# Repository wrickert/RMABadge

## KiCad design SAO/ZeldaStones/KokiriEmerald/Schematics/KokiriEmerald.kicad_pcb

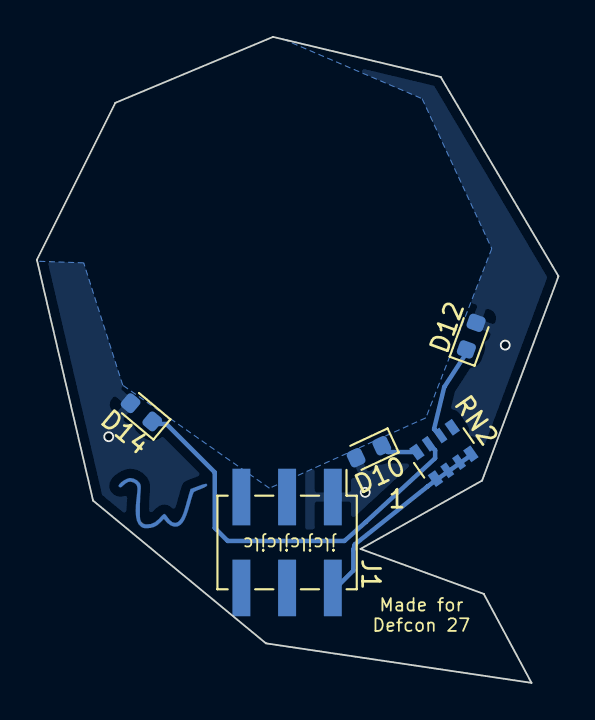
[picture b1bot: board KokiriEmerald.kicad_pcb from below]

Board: 2 copper layers, 29.0 x 35.9 mm, 6 parts (6 on the bottom side), 5 nets.

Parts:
D10, D12, D14: LED_Small; LED_0603_1608Metric
J1: Conn_02x03_Odd_Even; PinHeader_2x03_P2.54mm_Vertical_SMD
RN2: 330; R_Array_Convex_4x0603
Ref**: Val**; W

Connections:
unnamed: D12.1, RN2.2
unnamed: D14.1, RN2.3
unnamed: D10.1, RN2.4
VCC: D10.2, D12.2, D14.2, J1.1
VSS: J1.2, RN2.5, RN2.6, RN2.7, RN2.8

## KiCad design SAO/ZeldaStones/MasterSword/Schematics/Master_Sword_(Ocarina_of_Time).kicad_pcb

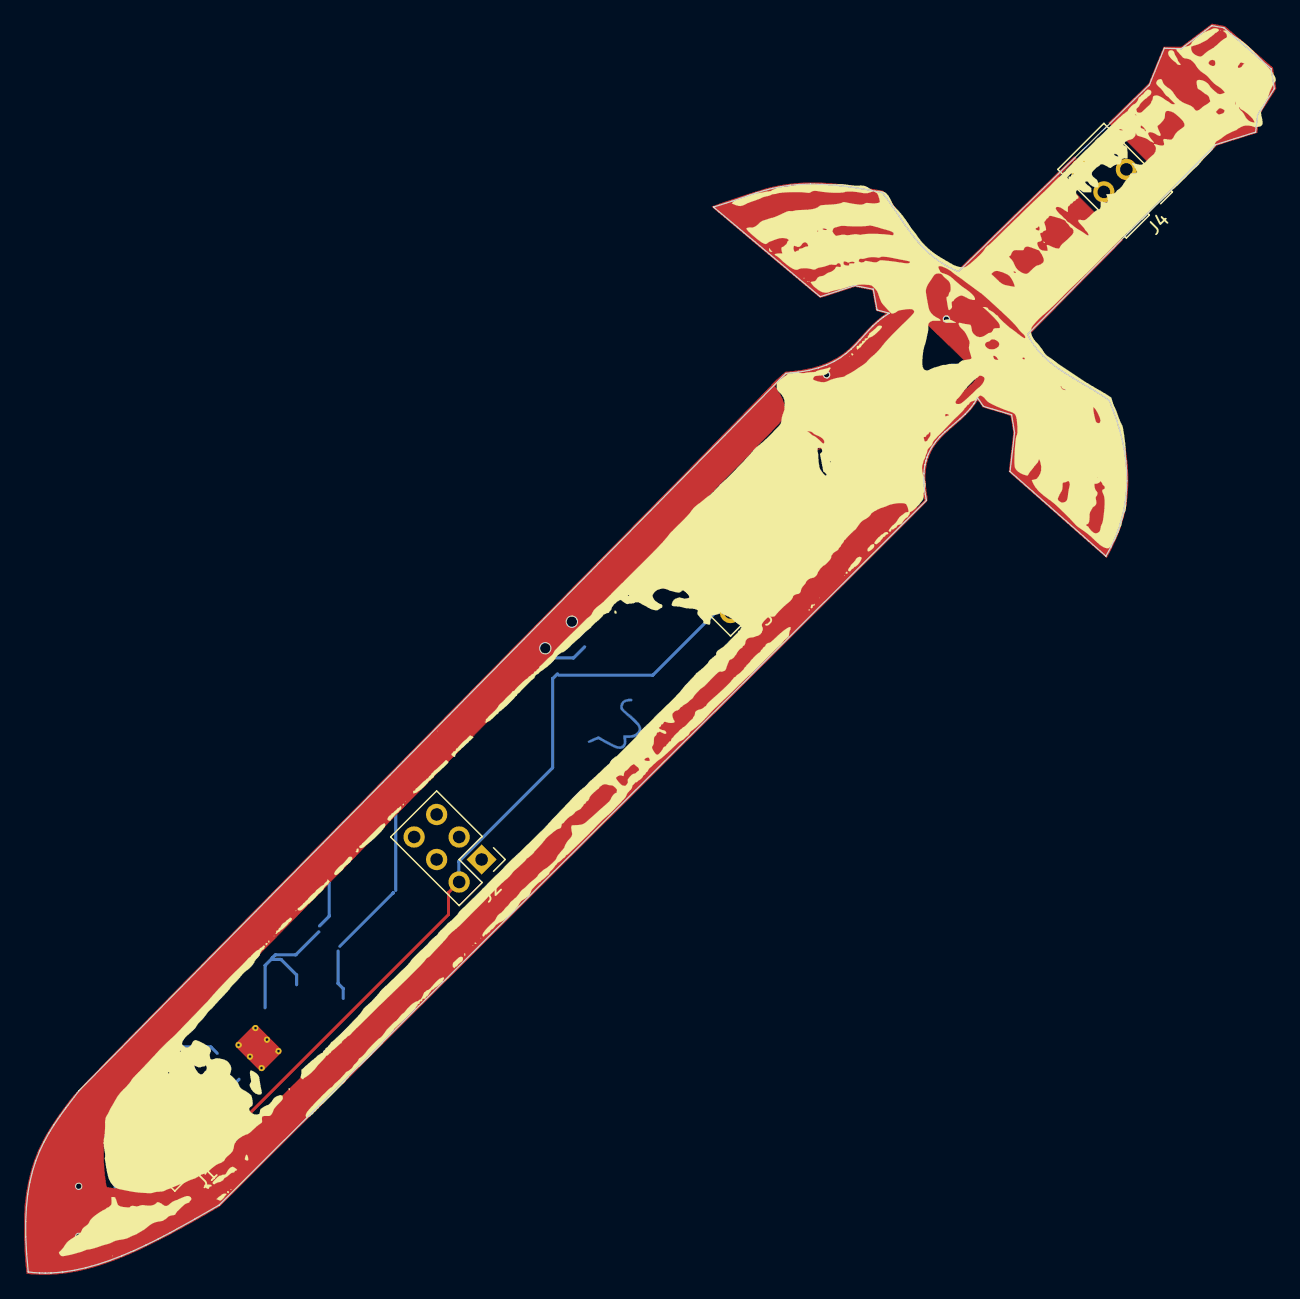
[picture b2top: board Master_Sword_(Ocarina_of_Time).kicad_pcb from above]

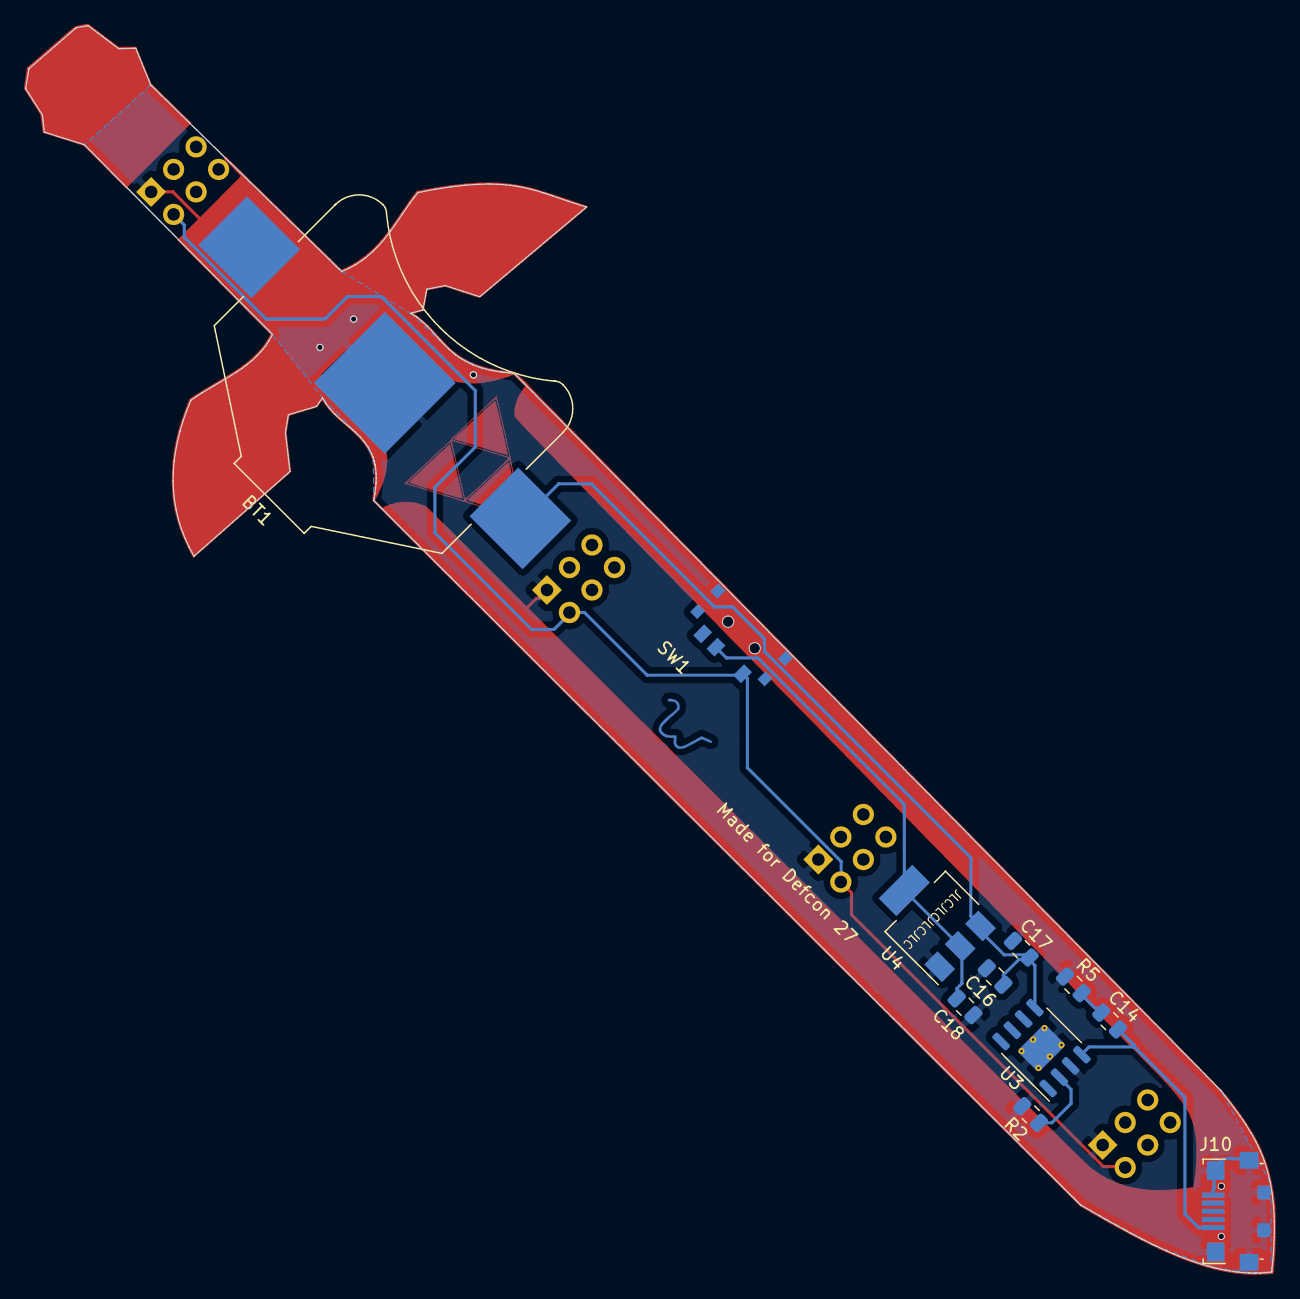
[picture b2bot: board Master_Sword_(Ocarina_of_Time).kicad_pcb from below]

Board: 2 copper layers, 99.7 x 99.6 mm, 16 parts (12 on the bottom side), 7 nets.

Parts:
BT1: Battery_Cell; BatteryHolder_Keystone_3008_1x2450
C14, C17: 10uF; C_0805_2012Metric
C16, C18: 1uF; C_0805_2012Metric
J1, J2, J3, J4: Conn_02x03_Odd_Even; PinHeader_2x03_P2.54mm_Vertical
J10: USB_B_Micro; USB_Micro-B_Jing
R2: 1k; R_0805_2012Metric
R5: 1.5; R_0805_2012Metric
Ref**: Val**; W
SW1: SW_SPDT; SK-3296S_switch
U3: HX4056; HSOP-8-1EP_3.9x4.9mm_P1.27mm_EP2.41x3.1mm_ThermalVias
U4: TLV1117-33; SOT-223-3_TabPin2

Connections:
+3V3: C18.1, SW1.2, U4.2
unnamed: C14.1, R5.2
unnamed: C14.2, J10.1, U3.4
unnamed: R2.1, U3.2
VDD: J1.2, J2.2, J3.2, J4.2, SW1.3
VDDA: BT1.1, C16.1, C17.2, U3.5, U4.3
VSS: BT1.2, C16.2, C17.1, C18.2, J1.1, J2.1, J3.1, J4.1, J10.5, J10.6, R2.2, R5.1, U3.3, U3.9, U4.1

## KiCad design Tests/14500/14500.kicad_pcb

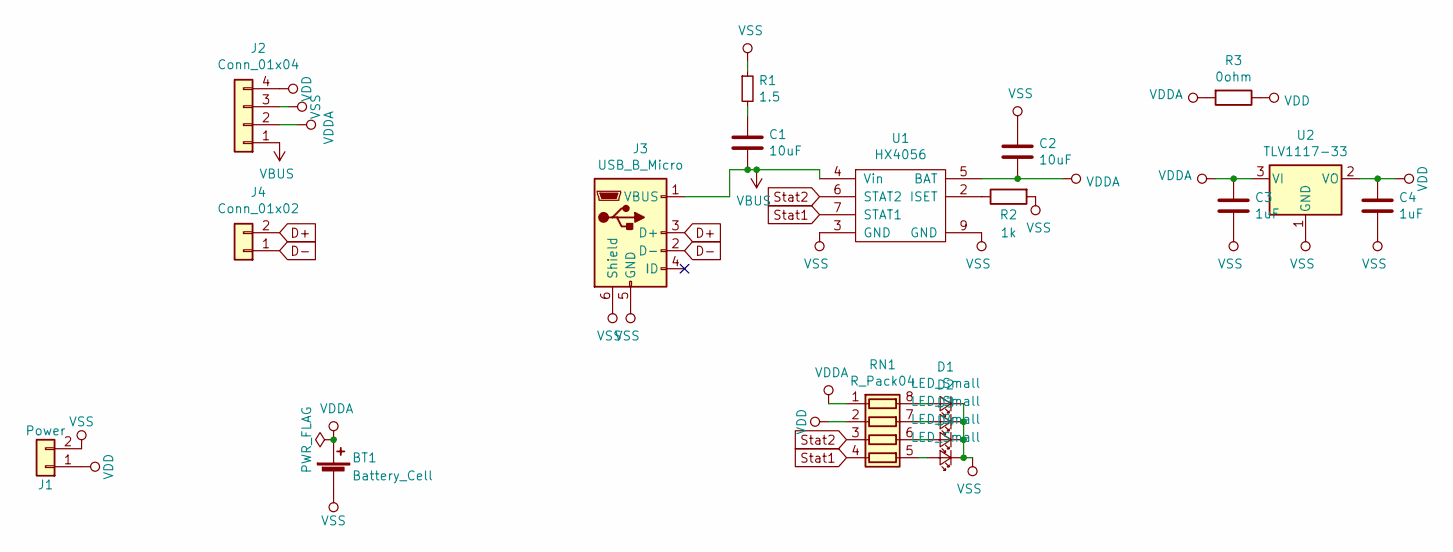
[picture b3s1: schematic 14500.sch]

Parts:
BT1: Battery_Cell; Dongguan14500
C1, C2: 10uF; C_0805_2012Metric
C3, C4: 1uF; C_0805_2012Metric
D1, D2, D3, D4: LED_Small; LED_0603_1608Metric
J1: Power; PinHeader_1x02_P2.54mm_Vertical
J2: Conn_01x04; PinHeader_1x04_P2.54mm_Vertical
J3: USB_B_Micro; USB_Micro-B_Jing
J4: Conn_01x02; PinHeader_1x02_P2.54mm_Vertical
R1: 1.5; R_0805_2012Metric
R2: 1k; R_0805_2012Metric
R3: 0ohm; R_0805_2012Metric
RN1: R_Pack04; R_Array_Concave_4x0603
U1: HX4056; HSOP-8-1EP_3.9x4.9mm_P1.27mm_EP2.41x3.1mm
U2: TLV1117-33; SOT-223-3_TabPin2

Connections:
D+: J3.3 (D+), J4.2
D-: J3.2 (D-), J4.1
unnamed: C1.1, R1.2
unnamed: D1.2 (A), RN1.8 (R1.2)
unnamed: D2.2 (A), RN1.7 (R2.2)
unnamed: D3.2 (A), RN1.6 (R3.2)
unnamed: D4.2 (A), RN1.5 (R4.2)
unnamed: R2.1, U1.2 (ISET)
Stat1: RN1.4 (R4.1), U1.7 (STAT1)
Stat2: RN1.3 (R3.1), U1.6 (STAT2)
VBUS: C1.2, J2.1, J3.1 (VBUS), U1.4 (Vin)
VDD: C4.1, J1.1, J2.4, R3.1, RN1.2 (R2.1), U2.2 (VO)
VDDA: BT1.1 (+), C2.2, C3.1, J2.2, R3.2, RN1.1 (R1.1), U1.5 (BAT), U2.3 (VI)
VSS: BT1.2 (-), C2.1, C3.2, C4.2, D1.1 (K), D2.1 (K), D3.1 (K), D4.1 (K), J1.2, J2.3, J3.5 (GND), J3.6 (Shield), R1.1, R2.2, U1.3 (GND), U1.9 (GND), U2.1 (GND)

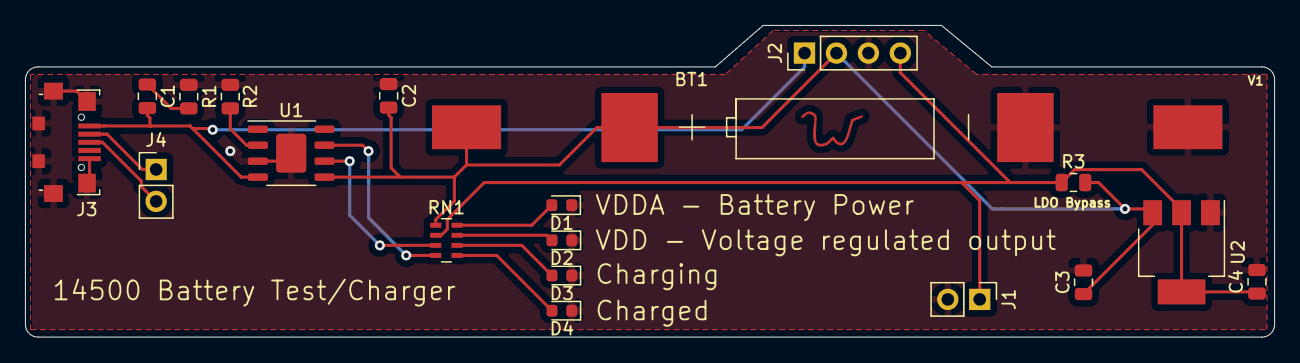
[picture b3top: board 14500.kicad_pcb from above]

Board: 2 copper layers, 99.4 x 24.8 mm, 20 parts (0 on the bottom side), 14 nets.

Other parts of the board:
Ref**: Val**; W

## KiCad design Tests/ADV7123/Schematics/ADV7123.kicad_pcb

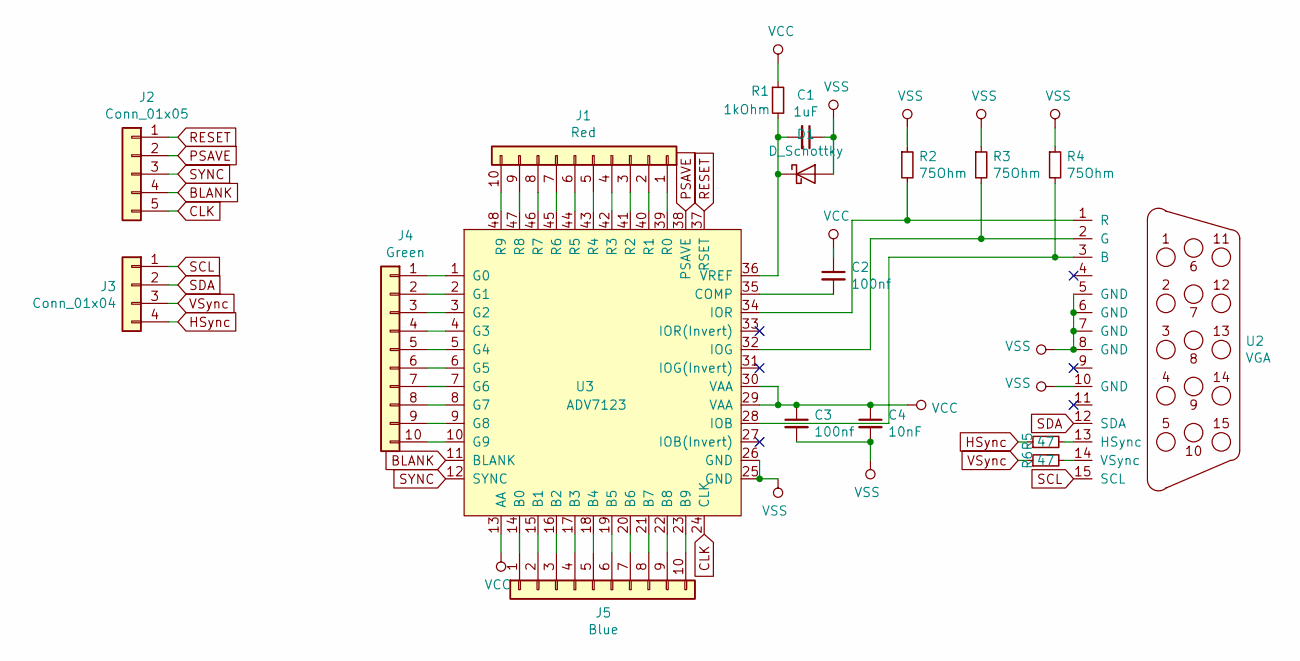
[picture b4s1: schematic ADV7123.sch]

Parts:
C1: 1uF; C_0805_2012Metric
C2, C3: 100nf; C_0805_2012Metric
C4: 10nF; C_0805_2012Metric
D1: D_Schottky; SOT-23
J1: Red; PinHeader_1x10_P2.54mm_Vertical
J2: Conn_01x05; PinHeader_1x05_P2.54mm_Vertical
J3: Conn_01x04; PinHeader_1x04_P2.54mm_Vertical
J4: Green; PinHeader_1x10_P2.54mm_Vertical
J5: Blue; PinHeader_1x10_P2.54mm_Vertical
R1: 1kOhm; R_0805_2012Metric
R2, R3, R4: 75Ohm; R_0805_2012Metric
R5, R6: 47; R_0805_2012Metric
U2: VGA; VGA-002
U3: ADV7123; LQFP-48_7x7mm_P0.5mm

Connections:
BLANK: J2.4, U3.11 (BLANK)
CLK: J2.5, U3.24 (CLK)
HSync: J3.4, R5.1
unnamed: C1.2, D1.1 (K), R1.2, U3.36 (VREF)
unnamed: C2.2, U3.35 (COMP)
unnamed: J1.1, U3.39 (R0)
unnamed: J1.2, U3.40 (R1)
unnamed: J1.3, U3.41 (R2)
unnamed: J1.4, U3.42 (R3)
unnamed: J1.5, U3.43 (R4)
unnamed: J1.6, U3.44 (R5)
unnamed: J1.7, U3.45 (R6)
unnamed: J1.8, U3.46 (R7)
unnamed: J1.9, U3.47 (R8)
unnamed: J1.10, U3.48 (R9)
unnamed: J4.1, U3.1 (G0)
unnamed: J4.2, U3.2 (G1)
unnamed: J4.3, U3.3 (G2)
unnamed: J4.4, U3.4 (G3)
unnamed: J4.5, U3.5 (G4)
unnamed: J4.6, U3.6 (G5)
unnamed: J4.7, U3.7 (G6)
unnamed: J4.8, U3.8 (G7)
unnamed: J4.9, U3.9 (G8)
unnamed: J4.10, U3.10 (G9)
unnamed: J5.1, U3.14 (B0)
unnamed: J5.2, U3.15 (B1)
unnamed: J5.3, U3.16 (B2)
unnamed: J5.4, U3.17 (B3)
unnamed: J5.5, U3.18 (B4)
unnamed: J5.6, U3.19 (B5)
unnamed: J5.7, U3.20 (B6)
unnamed: J5.8, U3.21 (B7)
unnamed: J5.9, U3.22 (B8)
unnamed: J5.10, U3.23 (B9)
unnamed: R2.2, U2.1 (R), U3.34 (IOR)
unnamed: R3.2, U2.2 (G), U3.32 (IOG)
unnamed: R4.2, U2.3 (B), U3.28 (IOB)
unnamed: R5.2, U2.13 (HSync)
unnamed: R6.2, U2.14 (VSync)
PSAVE: J2.2, U3.38 (PSAVE)
RESET: J2.1, U3.37 (RSET)
SCL: J3.1, U2.15 (SCL)
SDA: J3.2, U2.12 (SDA)
SYNC: J2.3, U3.12 (SYNC)
VCC: C2.1, C3.1, C4.1, R1.1, U3.13 (AA), U3.29 (VAA), U3.30 (VAA)
VSS: C1.1, C3.2, C4.2, D1.2 (A), R2.1, R3.1, R4.1, U2.5 (GND), U2.6 (GND), U2.7 (GND), U2.8 (GND), U2.10 (GND), U3.25 (GND), U3.26 (GND)
VSync: J3.3, R6.1

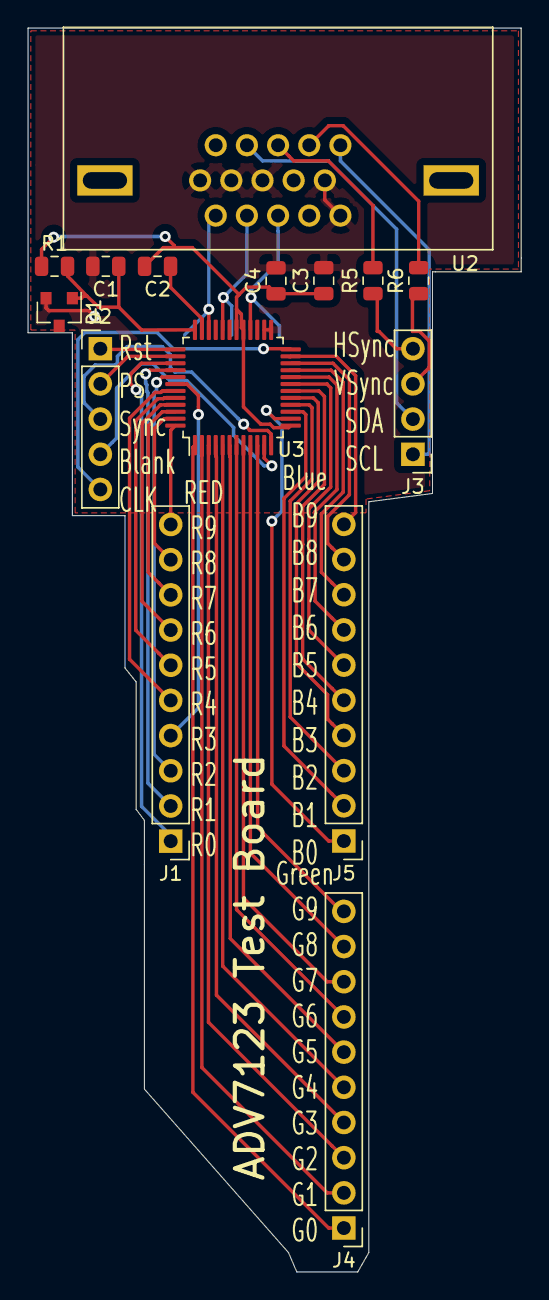
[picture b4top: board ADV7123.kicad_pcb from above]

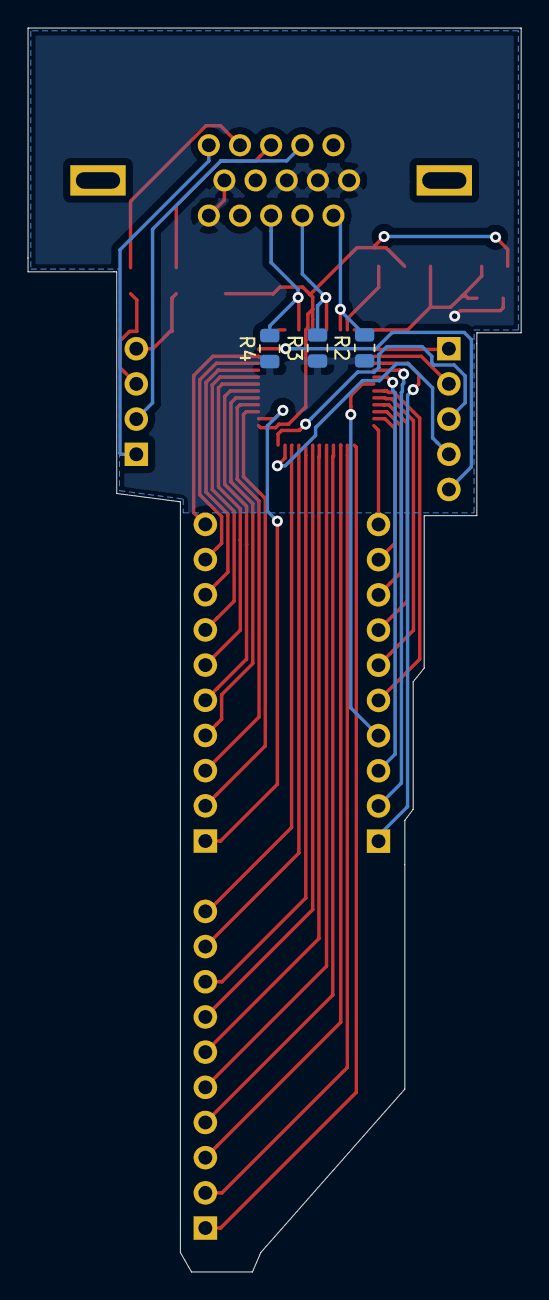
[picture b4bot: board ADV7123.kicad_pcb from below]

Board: 2 copper layers, 35.6 x 89.8 mm, 18 parts (3 on the bottom side), 48 nets.

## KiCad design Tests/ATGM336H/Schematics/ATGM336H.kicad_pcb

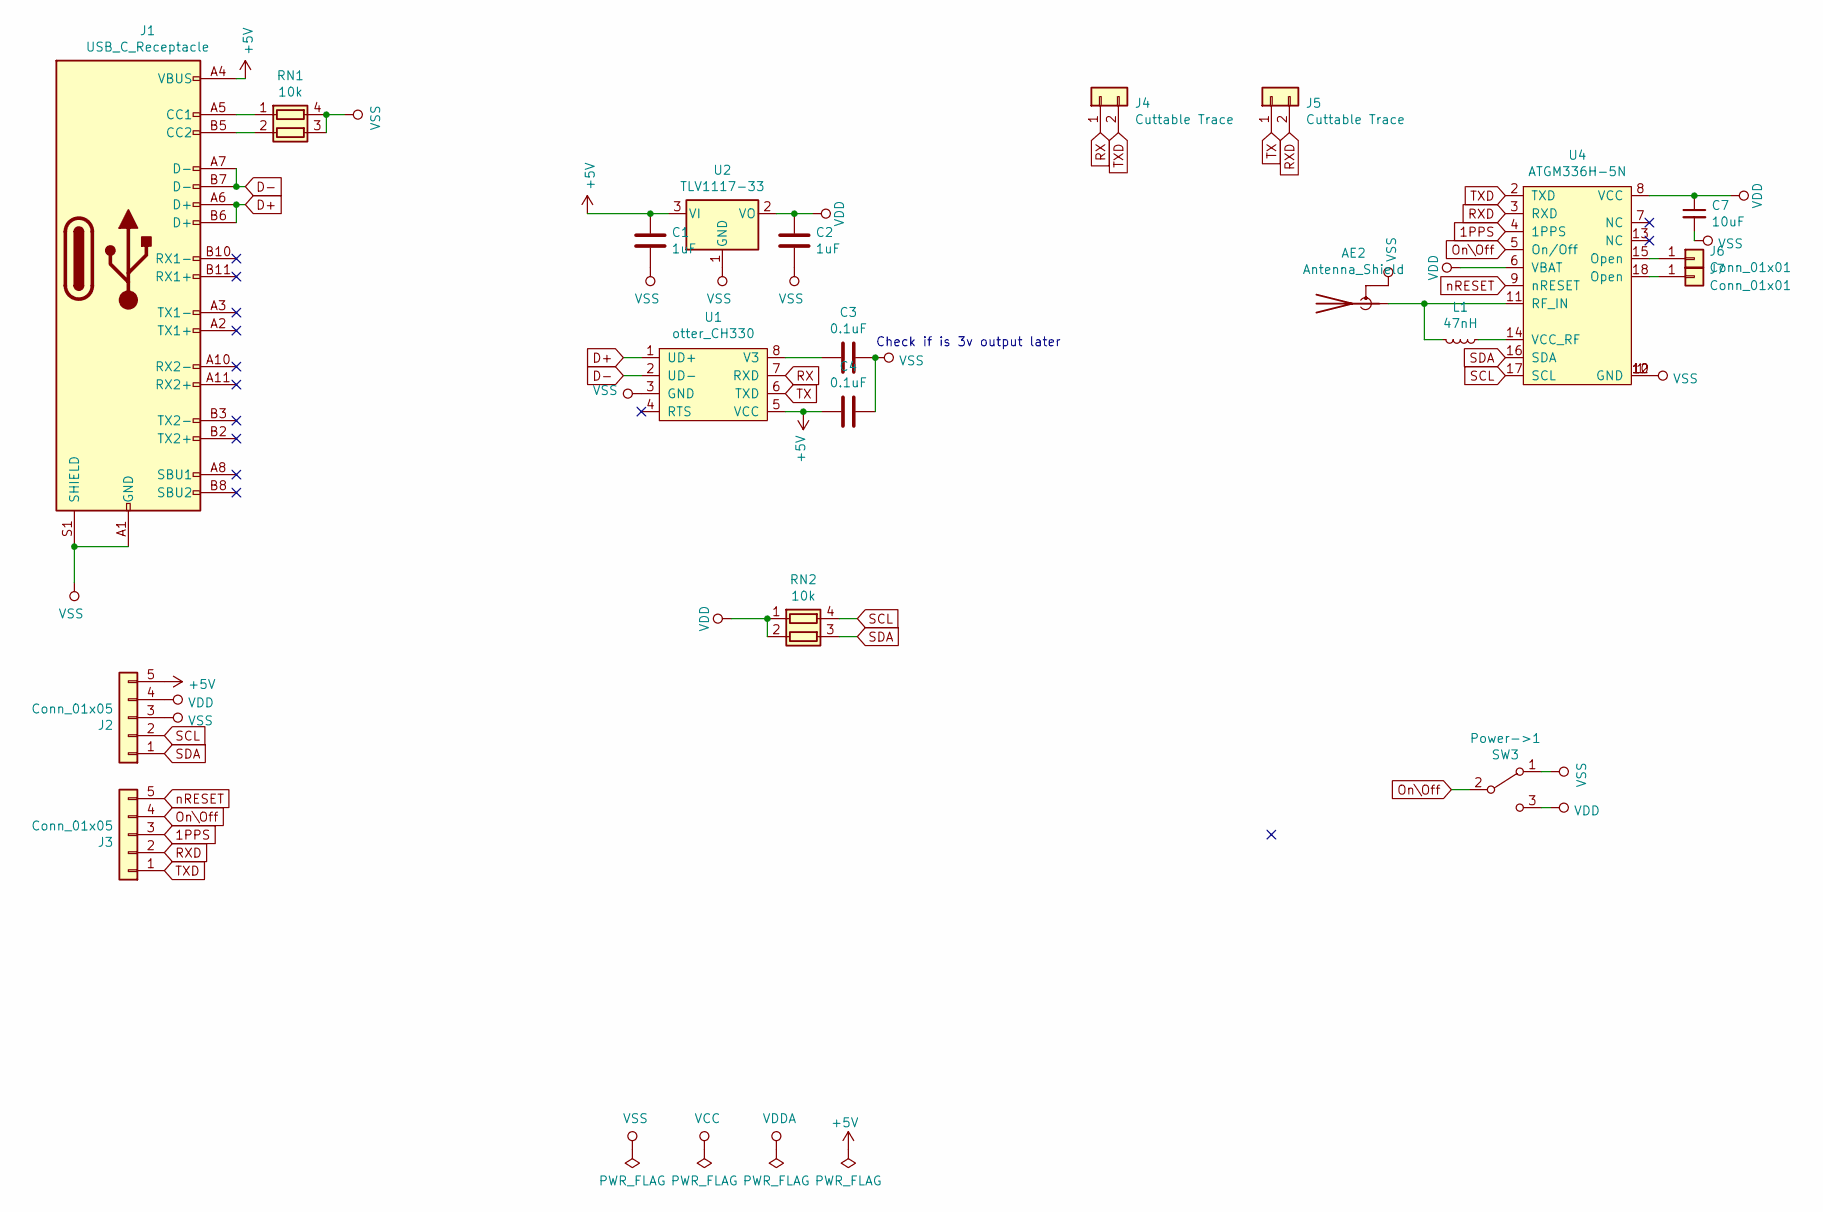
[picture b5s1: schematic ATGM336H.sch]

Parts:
AE2: Antenna_Shield; ECT818000071
C1, C2: 1uF; C_0805_2012Metric
C3, C4: 0.1uF; C_0805_2012Metric
C7: 10uF; C_0805_2012Metric
J1: USB_C_Receptacle; USB_C_Receptical-Jing
J2, J3: Conn_01x05; PinHeader_1x05_P2.54mm_Vertical
J4, J5: Cuttable Trace; CuttableTrace
J6, J7: Conn_01x01; PinHeader_1x01_P2.54mm_Vertical
L1: 47nH; L_0805_2012Metric
Power->1: SW3; SK-3296S_switch
RN1: 10k; R_Array_Convex_2x0603
RN2: 10k; R_Array_Convex_2x0606
U1: otter_CH330; SOIC-8_3.9x4.9mm_P1.27mm
U2: TLV1117-33; SOT-223-3_TabPin2
U4: ATGM336H-5N; ATGM336H

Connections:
1PPS: J3.3, U4.4 (1PPS)
+5V: C1.1, C4.2, J1.A4 (VBUS), J1.A9 (VBUS), J1.B4 (VBUS), J1.B9 (VBUS), J2.5, U1.5 (VCC), U2.3 (VI)
D+: J1.A6 (D+), J1.B6 (D+), U1.1 (UD+)
D-: J1.A7 (D-), J1.B7 (D-), U1.2 (UD-)
unnamed: AE2.1 (A), L1.2, U4.11 (RF_IN)
unnamed: C3.1, U1.8 (V3)
unnamed: J1.A5 (CC1), RN1.1 (R1.1)
unnamed: J1.B5 (CC2), RN1.2 (R2.1)
unnamed: J6.1, U4.15 (Open)
unnamed: J7.1, U4.18 (Open)
unnamed: L1.1, U4.14 (VCC_RF)
On\Off: J3.4, Power->1.2 (B), U4.5 (On/Off); also elsewhere on the board
RX: J4.1, U1.7 (RXD)
RXD: J3.2, J5.2, U4.3 (RXD)
SCL: J2.2, RN2.4 (R1.2), U4.17 (SCL)
SDA: J2.1, RN2.3 (R2.2), U4.16 (SDA)
TX: J5.1, U1.6 (TXD)
TXD: J3.1, J4.2, U4.2 (TXD)
VDD: C2.1, C7.1, J2.4, Power->1.3 (C), RN2.1 (R1.1), RN2.2 (R2.1), U2.2 (VO), U4.6 (VBAT), U4.8 (VCC); also elsewhere on the board
VSS: AE2.2 (Shield), C1.2, C2.2, C3.2, C4.1, C7.2, J1.A1 (GND), J1.A12 (GND), J1.B1 (GND), J1.B12 (GND), J1.S1 (SHIELD), J2.3, Power->1.1 (A), RN1.3 (R2.2), RN1.4 (R1.2), U1.3 (GND), U2.1 (GND), U4.1 (GND), U4.10 (GND), U4.12 (GND); also elsewhere on the board
nRESET: J3.5, U4.9 (nRESET)

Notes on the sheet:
Check if is 3v output later

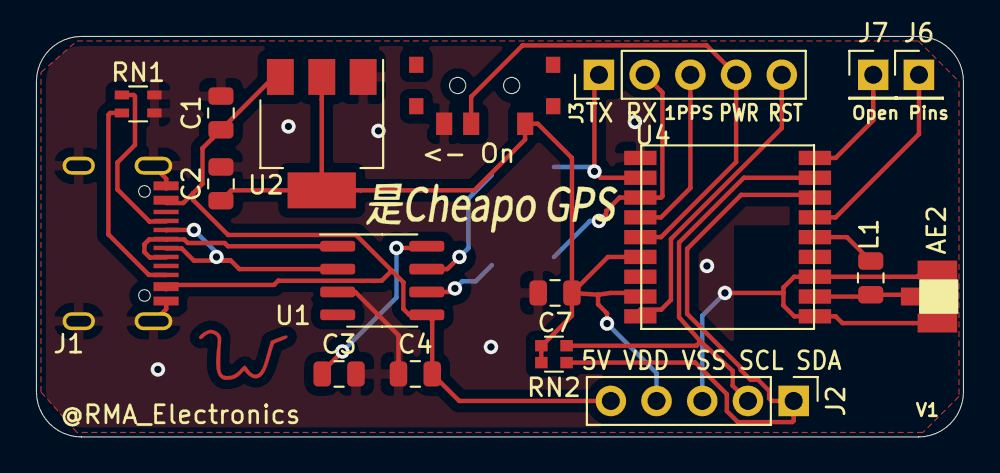
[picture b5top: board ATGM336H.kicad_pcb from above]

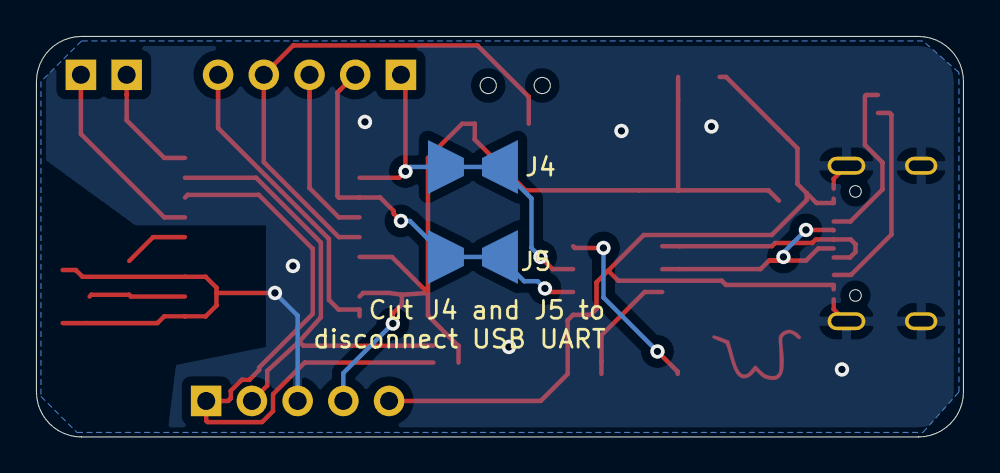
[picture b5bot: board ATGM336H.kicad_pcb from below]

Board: 2 copper layers, 51.5 x 22.2 mm, 22 parts (2 on the bottom side), 21 nets.

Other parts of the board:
<- On: SW3; SK-3296S_switch
Ref**: Val**; W
Ref**#2: Val**; GPSLogo

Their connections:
On\Off: <- On.2; also elsewhere on the board
VDD: <- On.3; also elsewhere on the board
VSS: <- On.1; also elsewhere on the board

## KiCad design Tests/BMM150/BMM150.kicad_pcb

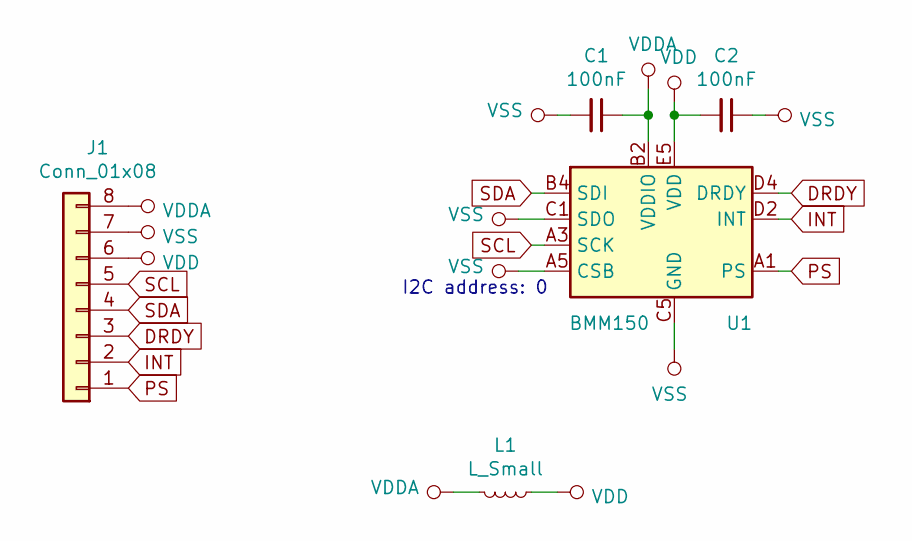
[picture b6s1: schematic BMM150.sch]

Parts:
C1, C2: 100nF; C_0805_2012Metric
J1: Conn_01x08; PinHeader_1x08_P2.54mm_Vertical
L1: L_Small; L_0805_2012Metric
U1: BMM150; WLCSP-12_1.56x1.56mm_P0.4mm

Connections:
DRDY: J1.3, U1.D4 (DRDY)
INT: J1.2, U1.D2 (INT)
PS: J1.1, U1.A1 (PS)
SCL: J1.5, U1.A3 (SCK)
SDA: J1.4, U1.B4 (SDI)
VDD: C2.2, J1.6, L1.1, U1.E5 (VDD)
VDDA: C1.1, J1.8, L1.2, U1.B2 (VDDIO)
VSS: C1.2, C2.1, J1.7, U1.A5 (CSB), U1.C1 (SDO), U1.C5 (GND), U1.E1 (GND), U1.E3 (GND)

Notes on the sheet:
I2C address: 0

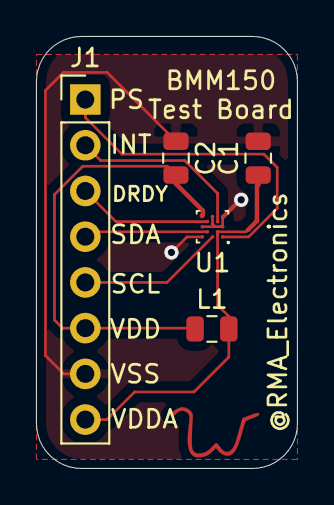
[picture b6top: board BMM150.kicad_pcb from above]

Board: 2 copper layers, 14.5 x 24.0 mm, 6 parts (0 on the bottom side), 8 nets.

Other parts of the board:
Ref**: Val**; W

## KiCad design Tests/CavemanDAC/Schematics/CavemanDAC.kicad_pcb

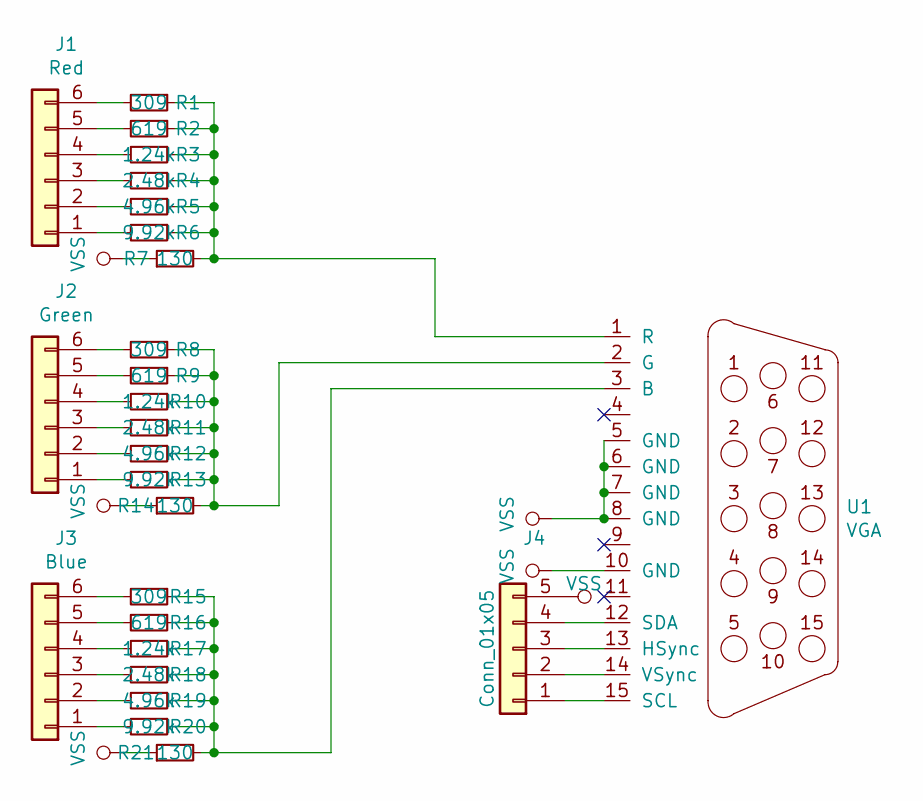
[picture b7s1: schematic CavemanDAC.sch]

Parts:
J1: Red; PinHeader_1x06_P2.54mm_Vertical
J2: Green; PinHeader_1x06_P2.54mm_Vertical
J3: Blue; PinHeader_1x06_P2.54mm_Vertical
J4: Conn_01x05; PinHeader_1x05_P2.54mm_Vertical
R1, R8, R15: 309; R_0805_2012Metric
R2, R9, R16: 619; R_0805_2012Metric
R3, R10, R17: 1.24k; R_0805_2012Metric
R4, R11, R18: 2.48k; R_0805_2012Metric
R5, R12, R19: 4.96k; R_0805_2012Metric
R6, R13, R20: 9.92k; R_0805_2012Metric
R7, R14, R21: 130; R_0805_2012Metric
U1: VGA; VGA-002

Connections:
unnamed: J1.1, R6.2
unnamed: J1.2, R5.2
unnamed: J1.3, R4.2
unnamed: J1.4, R3.2
unnamed: J1.5, R2.2
unnamed: J1.6, R1.2
unnamed: J2.1, R13.2
unnamed: J2.2, R12.2
unnamed: J2.3, R11.2
unnamed: J2.4, R10.2
unnamed: J2.5, R9.2
unnamed: J2.6, R8.2
unnamed: J3.1, R20.2
unnamed: J3.2, R19.2
unnamed: J3.3, R18.2
unnamed: J3.4, R17.2
unnamed: J3.5, R16.2
unnamed: J3.6, R15.2
unnamed: J4.1, U1.15 (SCL)
unnamed: J4.2, U1.14 (VSync)
unnamed: J4.3, U1.13 (HSync)
unnamed: J4.4, U1.12 (SDA)
unnamed: R1.1, R2.1, R3.1, R4.1, R5.1, R6.1, R7.2, U1.1 (R)
unnamed: R8.1, R9.1, R10.1, R11.1, R12.1, R13.1, R14.2, U1.2 (G)
unnamed: R15.1, R16.1, R17.1, R18.1, R19.1, R20.1, R21.2, U1.3 (B)
VSS: J4.5, R7.1, R14.1, R21.1, U1.5 (GND), U1.6 (GND), U1.7 (GND), U1.8 (GND), U1.10 (GND)

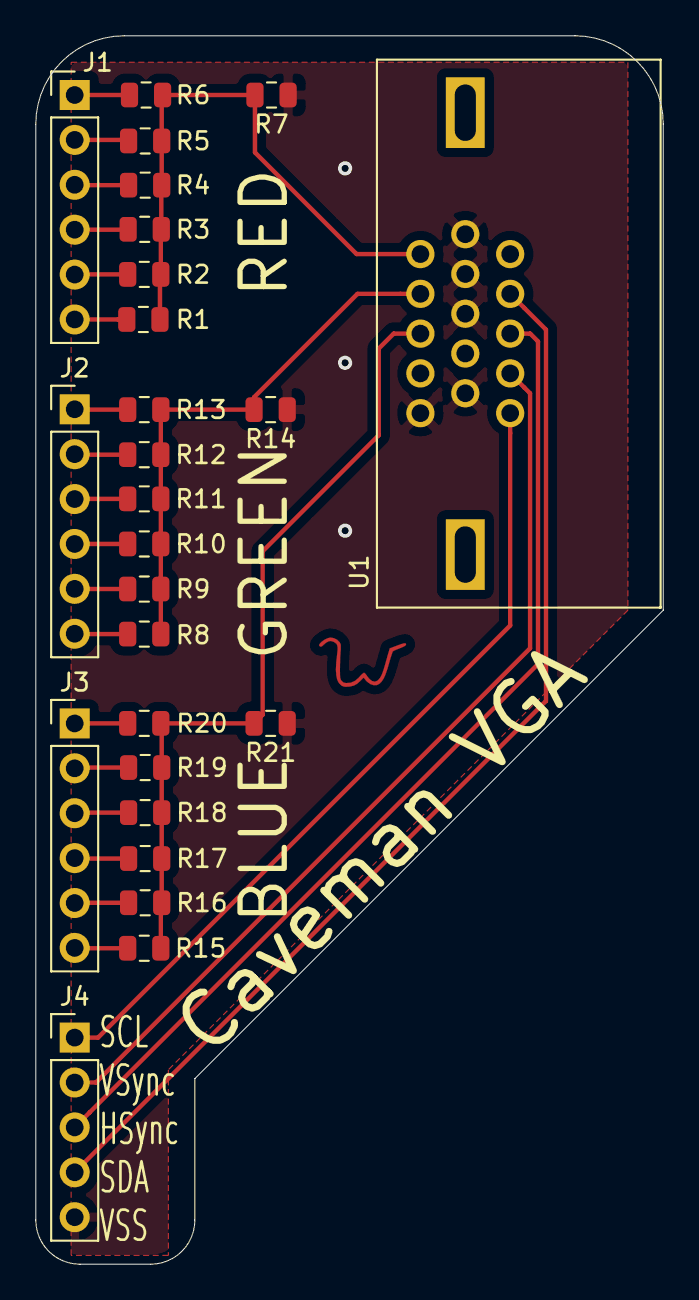
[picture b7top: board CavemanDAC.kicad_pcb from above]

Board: 2 copper layers, 35.5 x 69.5 mm, 27 parts (0 on the bottom side), 26 nets.

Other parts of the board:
Ref**: Val**; W

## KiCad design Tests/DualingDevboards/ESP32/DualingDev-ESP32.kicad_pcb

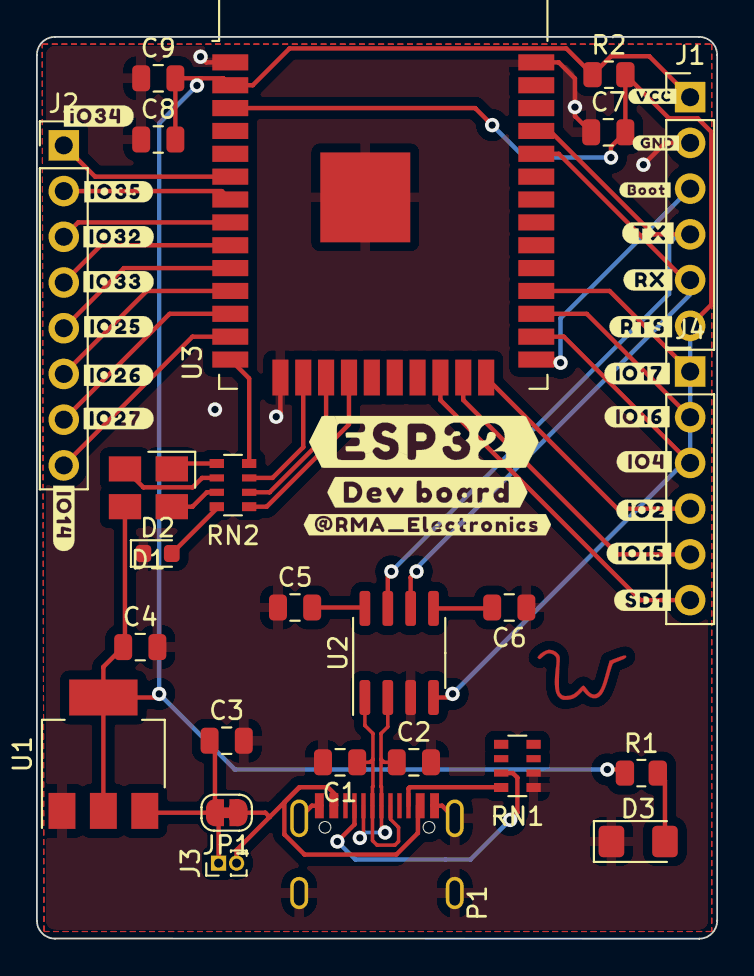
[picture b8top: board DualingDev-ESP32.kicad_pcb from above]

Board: 2 copper layers, 37.8 x 50.1 mm, 26 parts (0 on the bottom side), 37 nets.

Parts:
C1, C2: 20pF; C_0805_2012Metric
C3, C4: 1uF; C_0805_2012Metric
C5, C6, C7, C9: 100nF; C_0805_2012Metric
C8: 10uF; C_0805_2012Metric
D1: LED_BGRA; EKINGLUX-E6
D2: LED; LED_0603_1608Metric
D3: POWER; LED_1206_3216Metric_Pad1.42x1.75mm_HandSolder
J1: Program; PinHeader_1x06_P2.54mm_Vertical
J2: Conn_01x08; PinHeader_1x08_P2.54mm_Vertical
J3: Conn_01x02; PinHeader_1x02_P1.00mm_Vertical
J4: Conn_01x06; PinHeader_1x06_P2.54mm_Vertical
JP1: Jumper_NC_Small; SolderJumper-2_P1.3mm_Bridged_RoundedPad1.0x1.5mm
P1: USB_C_Plug_corrected; USB_C_Receptical-Jing
R1: R; R_0805_2012Metric
R2: 10k; R_0805_2012Metric
RN1: 5.1k; R_Array_Convex_4x0603
RN2: 270; R_Array_Convex_4x0603
Ref**: Val**; W
U1: TLV1117-33; SOT-223-3_TabPin2
U2: CH330N; SOIC-8_3.9x4.9mm_P1.27mm
U3: ESP32-WROOM-32

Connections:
1: J2.1, U3.6 (IO34)
2: J2.2, U3.7 (IO35)
3: J2.3, U3.8 (IO32)
4: J2.4, U3.9 (IO33)
5: J2.5, U3.10 (IO25)
6: J2.6, U3.11 (IO26)
7: J2.7, U3.12 (IO27)
8: J2.8, U3.13 (IO14)
/D+: C1.1, P1.A6 (D+), P1.B6 (D+), U2.1 (UD+)
/D-: C2.1, P1.A7 (D-), P1.B7 (D-), U2.2 (UD-)
A: J4.1, U3.28 (IO17)
Attention: RN2.1 (R1.1), U3.18 (SWP/SD3)
B: J4.2, U3.27 (IO16)
Blue: RN2.4 (R4.1), U3.14 (IO12)
Boot: J1.3, U3.25 (IO0)
C: J4.3, U3.26 (IO4)
D: J4.4, U3.24 (IO2)
E: J4.5, U3.23 (IO15)
F: J4.6, U3.22 (SDI/SD1)
GND: C1.2, C2.2, C3.2, C4.2, C5.1, C6.1, C7.1, C8.1, C9.1, D2.1 (K), D3.1 (K), J1.2, P1.A1 (GND), P1.A12 (GND), P1.B1 (GND), P1.B12 (GND), P1.S1 (SHIELD), RN1.1 (R1.1), RN1.2 (R2.1), U1.1 (GND), U2.3 (GND), U3.1 (GND), U3.15 (GND), U3.38 (GND), U3.39 (GND)
Green: RN2.3 (R3.1), U3.16 (IO13)
unnamed: C3.1, J3.1, JP1.2, U1.3 (VI)
unnamed: C5.2, U2.8 (V3)
unnamed: C6.2, U2.5 (VCC)
unnamed: D1.1 (BK), RN2.5 (R4.2)
unnamed: D1.2 (GK), RN2.6 (R3.2)
unnamed: D1.3 (RK), RN2.7 (R2.2)
unnamed: D2.2 (A), RN2.8 (R1.2)
unnamed: D3.2 (A), R1.2
unnamed: P1.A5 (CC), RN1.7 (R2.2)
unnamed: P1.B5 (VCONN), RN1.8 (R1.2)
RTS: C7.2, J1.6, R2.2, U2.4 (~RTS), U3.3 (EN)
RX: J1.5, U2.6 (TXD), U3.34 (RXD0/IO3)
Red: RN2.2 (R2.1), U3.17 (SHD/SD2)
TX: J1.4, U2.7 (RXD), U3.35 (TXD0/IO1)
VBUS: J3.2, JP1.1, P1.A4 (VBUS), P1.A9 (VBUS), P1.B4 (VBUS), P1.B9 (VBUS)
VCC: C4.1, C8.2, C9.2, D1.4 (A), J1.1, R1.1, R2.1, U1.2 (VO), U3.2 (VDD)
